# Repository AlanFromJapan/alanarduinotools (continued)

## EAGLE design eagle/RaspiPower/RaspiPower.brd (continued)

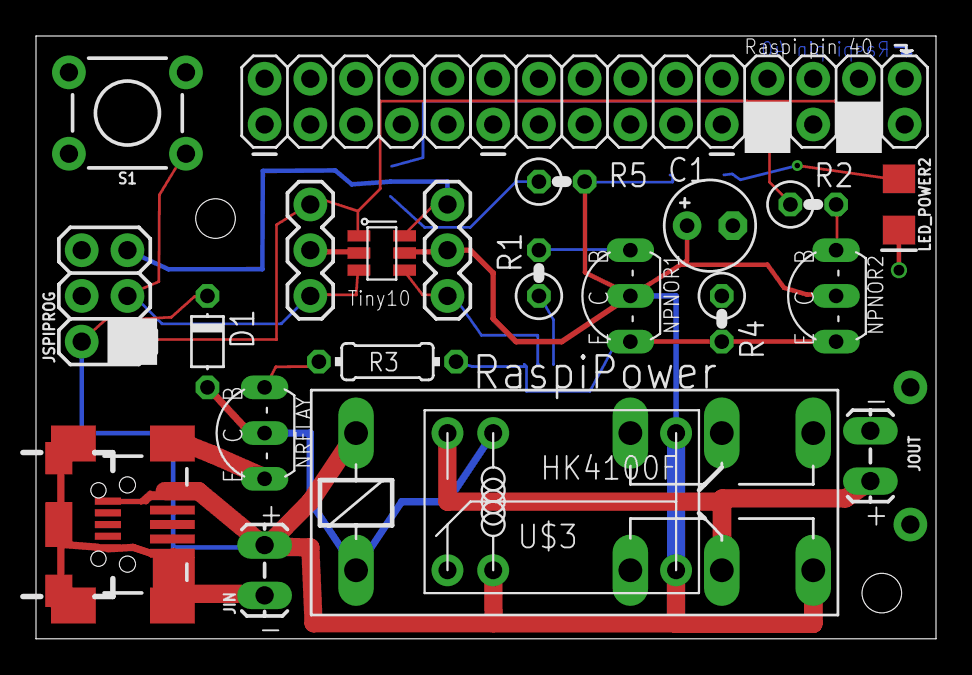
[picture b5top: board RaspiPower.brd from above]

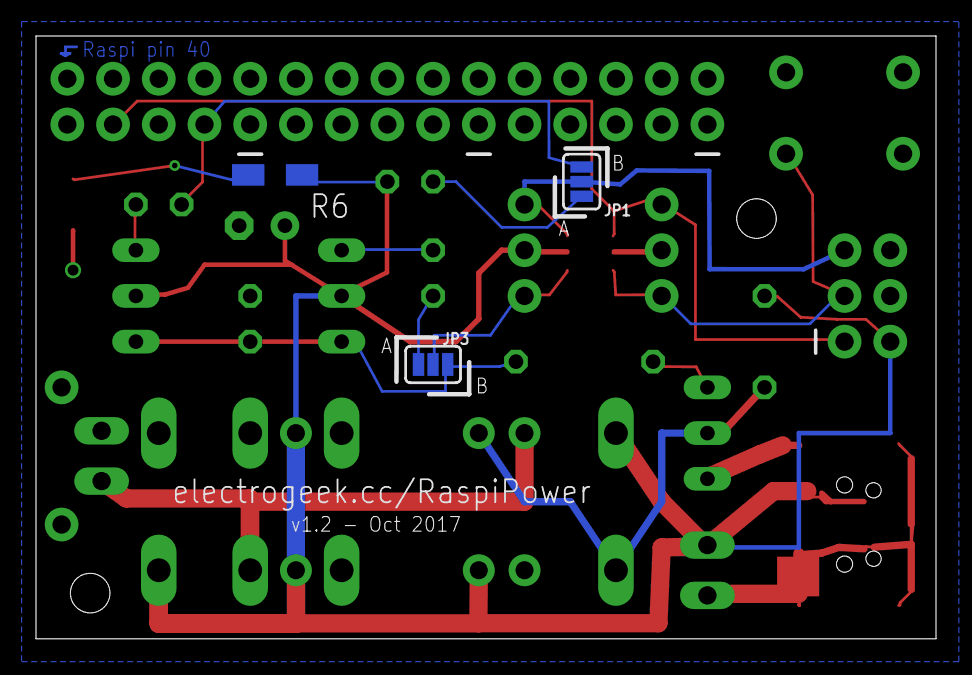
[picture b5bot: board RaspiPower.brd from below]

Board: 2 copper layers, 50.0 x 33.5 mm, 30 parts (3 on the bottom side), 16 nets.

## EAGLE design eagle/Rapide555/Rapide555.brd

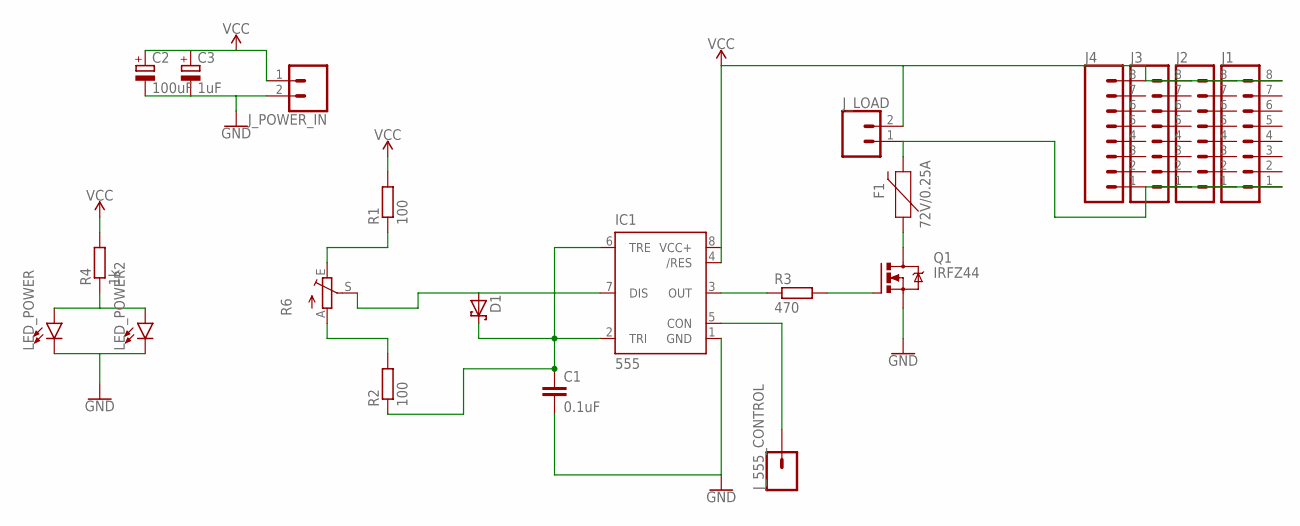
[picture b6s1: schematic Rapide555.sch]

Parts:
C1: 0.1uF; C025-025X050
C2: 100uF; E5-5
C3: 1uF; E2,5-6E
D1: SCHOTTKY-DIODEDO35-7; DO35-7
F1: 72V/0.25A; PTH
IC1: 555; DIP08
J1, J2, J3, J4: CONN_08NO_SILK_FEMALE_PTH; 1X08_NO_SILK
J_555_CONTROL: CONN_01; 1X01
J_LOAD: CONN_023.5MM; SCREWTERMINAL-3.5MM-2
J_POWER_IN: CONN_023.5MM; SCREWTERMINAL-3.5MM-2
LED_POWER: LED3MM; LED_3MM
LED_POWER2: LED-FKIT-1206; FKIT-LED-1206
Q1: IRFZ44; TO-247AD-V
R1: 100; 0204/5
R2: 100; 0204V
R3: 470; 0204/5
R4: 1k; 0204V
R6: TRIM_EU-B25P; B25P

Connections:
GND: C1.2, C2.-, C3.-, IC1.1 (GND), J_POWER_IN.2, LED_POWER.K (C), LED_POWER2.C, Q1.S
unnamed: D1.A, IC1.7 (DIS), R6.S
unnamed: F1.P$2 (2), J1.1, J2.1, J3.1, J4.1, J_LOAD.1
unnamed: F1.P$1 (1), Q1.D
unnamed: IC1.5 (CON), J_555_CONTROL.1
unnamed: IC1.3 (OUT), R3.1
unnamed: Q1.G, R3.2
unnamed: C1.1, D1.C, IC1.2 (TRI), IC1.6 (TRE), R2.1
unnamed: R1.1, R6.E
unnamed: R2.2, R6.A
unnamed: LED_POWER.A, LED_POWER2.A, R4.1
VCC: C2.+, C3.+, IC1.4 (/RES), IC1.8 (VCC+), J1.8, J2.8, J3.8, J4.8, J_LOAD.2, J_POWER_IN.1, R1.2, R4.2

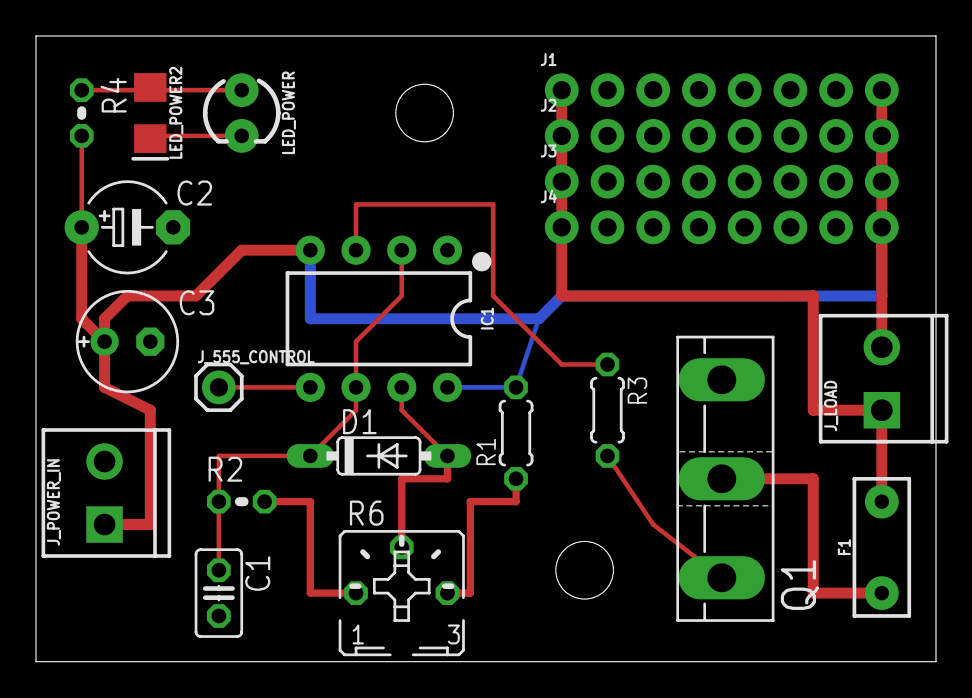
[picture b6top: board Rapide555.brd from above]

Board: 2 copper layers, 50.0 x 34.8 mm, 21 parts (0 on the bottom side), 12 nets.

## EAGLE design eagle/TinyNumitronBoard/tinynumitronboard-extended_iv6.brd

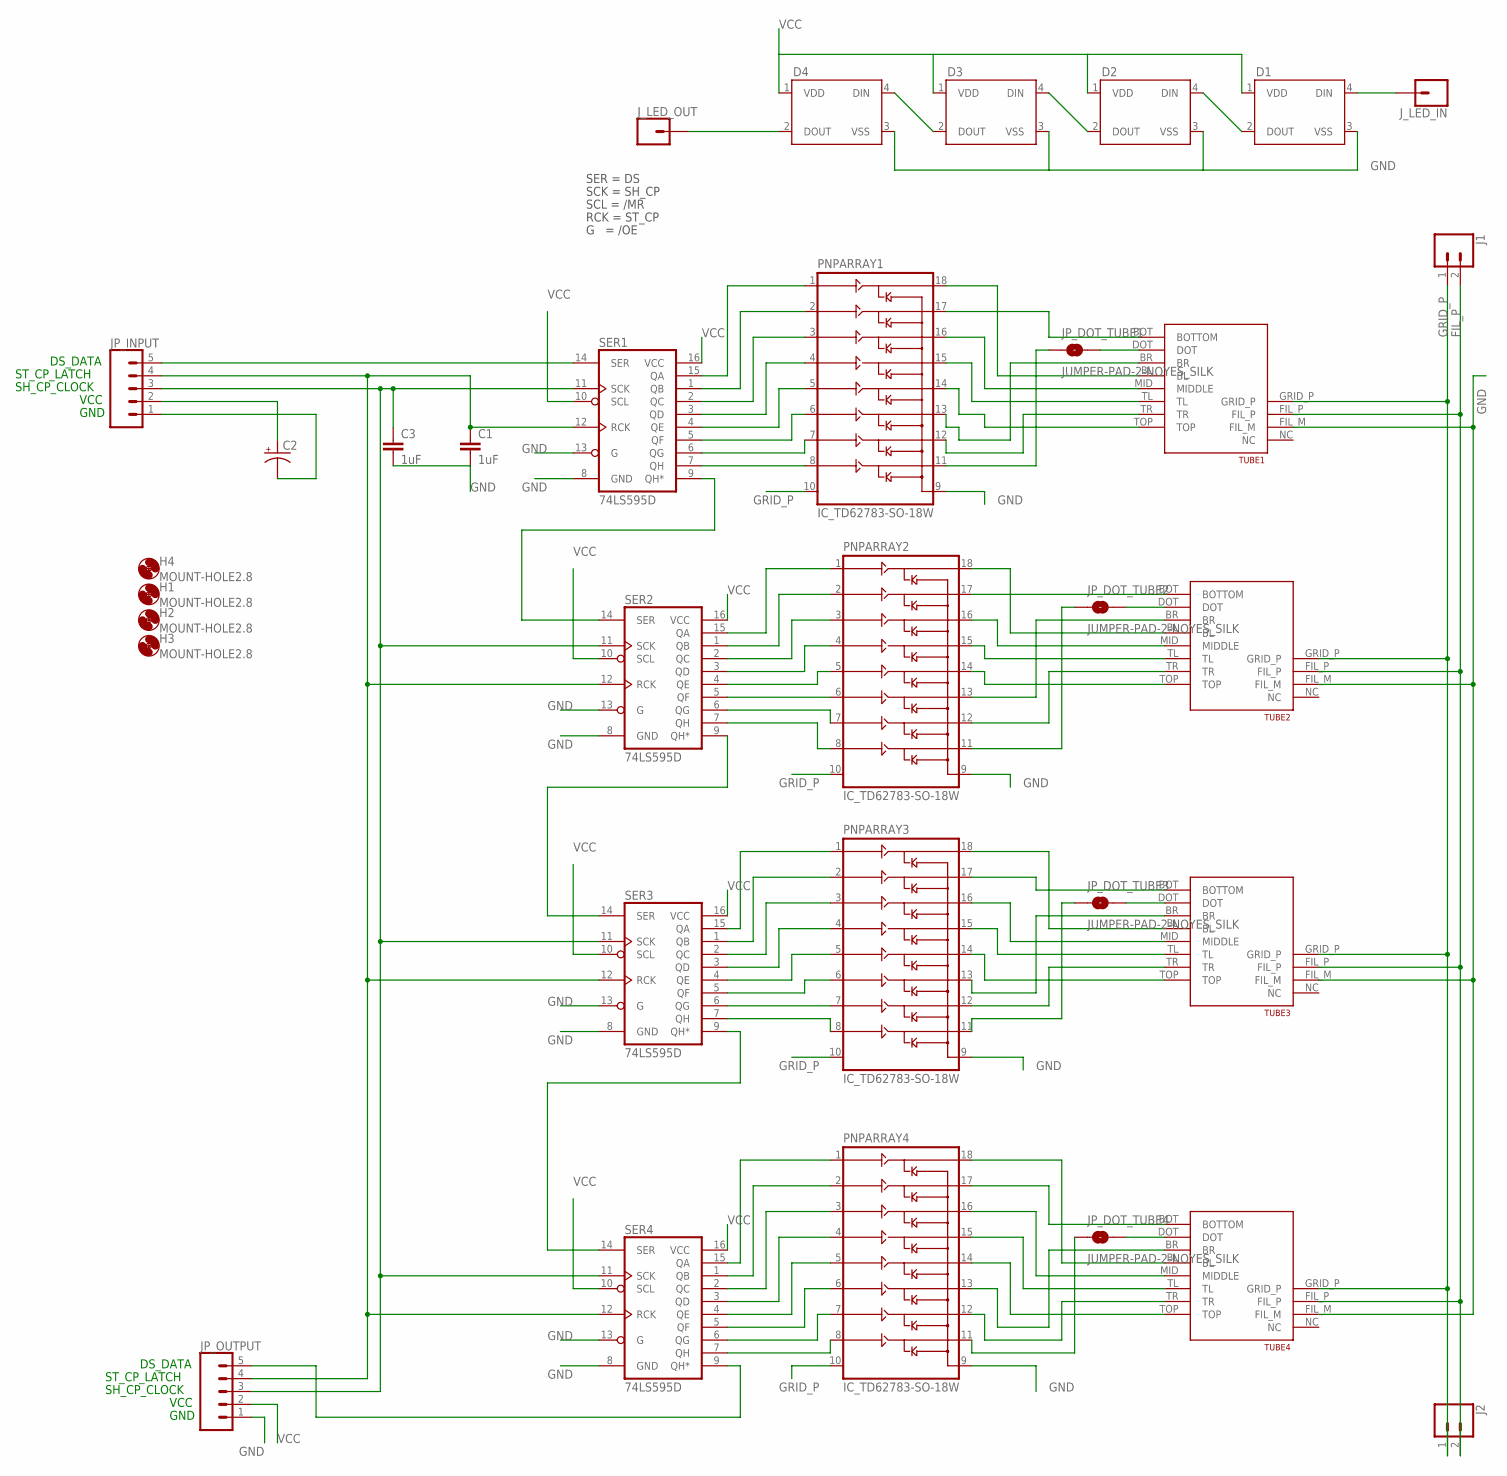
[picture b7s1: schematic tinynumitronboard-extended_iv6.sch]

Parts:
C1, C3: 1uF; C1206
C2: CAP_POLD; PANASONIC_D
D1, D2, D3, D4: WS2812B
H1, H2, H3, H4: MOUNT-HOLE2.8; 2,8
J1, J2: CONN_021X02_NO_SILK; 1X02_NO_SILK
JP_DOT_TUBE1, JP_DOT_TUBE2, JP_DOT_TUBE3, JP_DOT_TUBE4: JUMPER-PAD-2-NOYES_SILK; PAD-JUMPER-2-NO_YES_SILK
JP_INPUT: CONN_05NO_SILK; 1X05_NO_SILK
JP_OUTPUT: CONN_05NO_SILK; 1X05_NO_SILK
J_LED_IN: CONN_01; 1X01
J_LED_OUT: CONN_01; 1X01
PNPARRAY1, PNPARRAY2, PNPARRAY3, PNPARRAY4: IC_TD62783-SO-18W; SO-18L
SER1, SER2, SER3, SER4: 74LS595D; SO16
TUBE1, TUBE2, TUBE3, TUBE4: IV6_NUMITRONLARGE; IV6_NUMITRON_PAC_LARGE

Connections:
FIL_P: J1.2, J2.2, TUBE1.FIL_P, TUBE2.FIL_P, TUBE3.FIL_P, TUBE4.FIL_P
GND: C1.2, C2.-, C3.2, D1.3 (VSS), D2.3 (VSS), D3.3 (VSS), D4.3 (VSS), JP_INPUT.1, JP_OUTPUT.1, PNPARRAY1.9 (GND), PNPARRAY2.9 (GND), PNPARRAY3.9 (GND), PNPARRAY4.9 (GND), SER1.8 (GND), SER1.13 (G), SER2.8 (GND), SER2.13 (G), SER3.8 (GND), SER3.13 (G), SER4.8 (GND), SER4.13 (G), TUBE1.FIL_M, TUBE2.FIL_M, TUBE3.FIL_M, TUBE4.FIL_M
GRID_P: J1.1, J2.1, PNPARRAY1.10 (VS), PNPARRAY2.10 (VS), PNPARRAY3.10 (VS), PNPARRAY4.10 (VS), TUBE1.GRID_P, TUBE2.GRID_P, TUBE3.GRID_P, TUBE4.GRID_P
unnamed: PNPARRAY1.5 (IN5), SER1.4 (QE)
unnamed: PNPARRAY1.4 (IN4), SER1.3 (QD)
unnamed: PNPARRAY1.3 (IN3), SER1.2 (QC)
unnamed: PNPARRAY1.2 (IN2), SER1.1 (QB)
unnamed: PNPARRAY1.1 (IN1), SER1.15 (QA)
unnamed: PNPARRAY1.6 (IN6), SER1.5 (QF)
unnamed: PNPARRAY1.7 (IN7), SER1.6 (QG)
unnamed: PNPARRAY1.8 (IN8), SER1.7 (QH)
unnamed: D1.2 (DOUT), D2.4 (DIN)
unnamed: D2.2 (DOUT), D3.4 (DIN)
unnamed: D3.2 (DOUT), D4.4 (DIN)
unnamed: D1.4 (DIN), J_LED_IN.1
unnamed: SER2.9 (QH*), SER3.14 (SER)
unnamed: PNPARRAY2.18 (OUT1), TUBE2.BL
unnamed: PNPARRAY1.18 (OUT1), TUBE1.BL
unnamed: PNPARRAY2.17 (OUT2), TUBE2.BOT (BOTTOM)
unnamed: PNPARRAY2.16 (OUT3), TUBE2.MID (MIDDLE)
unnamed: PNPARRAY1.17 (OUT2), TUBE1.BOT (BOTTOM)
unnamed: PNPARRAY1.16 (OUT3), TUBE1.MID (MIDDLE)
unnamed: SER1.9 (QH*), SER2.14 (SER)
unnamed: PNPARRAY4.18 (OUT1), TUBE4.BL
unnamed: PNPARRAY4.17 (OUT2), TUBE4.BOT (BOTTOM)
unnamed: PNPARRAY4.16 (OUT3), TUBE4.MID (MIDDLE)
unnamed: PNPARRAY4.15 (OUT4), TUBE4.TL
unnamed: PNPARRAY4.14 (OUT5), TUBE4.TOP
unnamed: PNPARRAY4.13 (OUT6), TUBE4.BR
unnamed: PNPARRAY4.12 (OUT7), TUBE4.TR
unnamed: JP_DOT_TUBE4.1, PNPARRAY4.11 (OUT8)
unnamed: PNPARRAY4.1 (IN1), SER4.15 (QA)
unnamed: PNPARRAY4.2 (IN2), SER4.1 (QB)
unnamed: PNPARRAY4.3 (IN3), SER4.2 (QC)
unnamed: PNPARRAY4.4 (IN4), SER4.3 (QD)
unnamed: PNPARRAY4.5 (IN5), SER4.4 (QE)
unnamed: PNPARRAY4.6 (IN6), SER4.5 (QF)
unnamed: PNPARRAY1.15 (OUT4), TUBE1.TL
unnamed: PNPARRAY2.15 (OUT4), TUBE2.TL
unnamed: PNPARRAY2.14 (OUT5), TUBE2.TOP
unnamed: PNPARRAY2.13 (OUT6), TUBE2.BR
unnamed: PNPARRAY2.12 (OUT7), TUBE2.TR
unnamed: JP_DOT_TUBE2.1, PNPARRAY2.11 (OUT8)
unnamed: PNPARRAY2.1 (IN1), SER2.15 (QA)
unnamed: PNPARRAY2.2 (IN2), SER2.1 (QB)
unnamed: PNPARRAY2.3 (IN3), SER2.2 (QC)
unnamed: PNPARRAY2.4 (IN4), SER2.3 (QD)
unnamed: PNPARRAY2.5 (IN5), SER2.4 (QE)
unnamed: PNPARRAY2.6 (IN6), SER2.5 (QF)
unnamed: PNPARRAY2.7 (IN7), SER2.6 (QG)
unnamed: PNPARRAY2.8 (IN8), SER2.7 (QH)
unnamed: PNPARRAY4.7 (IN7), SER4.6 (QG)
unnamed: SER3.9 (QH*), SER4.14 (SER)
unnamed: PNPARRAY3.18 (OUT1), TUBE3.BL
unnamed: PNPARRAY1.14 (OUT5), TUBE1.TOP
unnamed: PNPARRAY1.13 (OUT6), TUBE1.BR
unnamed: PNPARRAY1.12 (OUT7), TUBE1.TR
unnamed: PNPARRAY3.17 (OUT2), TUBE3.BOT (BOTTOM)
unnamed: JP_DOT_TUBE1.1, PNPARRAY1.11 (OUT8)
unnamed: PNPARRAY3.16 (OUT3), TUBE3.MID (MIDDLE)
unnamed: PNPARRAY3.15 (OUT4), TUBE3.TL
unnamed: PNPARRAY3.14 (OUT5), TUBE3.TOP
unnamed: PNPARRAY3.13 (OUT6), TUBE3.BR
unnamed: PNPARRAY3.12 (OUT7), TUBE3.TR
unnamed: JP_DOT_TUBE3.1, PNPARRAY3.11 (OUT8)
unnamed: PNPARRAY3.1 (IN1), SER3.15 (QA)
unnamed: PNPARRAY3.2 (IN2), SER3.1 (QB)
unnamed: PNPARRAY3.3 (IN3), SER3.2 (QC)
unnamed: PNPARRAY3.4 (IN4), SER3.3 (QD)
unnamed: PNPARRAY3.5 (IN5), SER3.4 (QE)
unnamed: PNPARRAY3.6 (IN6), SER3.5 (QF)
unnamed: PNPARRAY3.7 (IN7), SER3.6 (QG)
unnamed: PNPARRAY3.8 (IN8), SER3.7 (QH)
unnamed: PNPARRAY4.8 (IN8), SER4.7 (QH)
unnamed: JP_DOT_TUBE2.2, TUBE2.DOT
unnamed: JP_DOT_TUBE3.2, TUBE3.DOT
unnamed: JP_DOT_TUBE1.2, TUBE1.DOT
unnamed: JP_DOT_TUBE4.2, TUBE4.DOT
unnamed: JP_OUTPUT.5, SER4.9 (QH*)
unnamed: D4.2 (DOUT), J_LED_OUT.1
RCK: C1.1, JP_INPUT.4, JP_OUTPUT.4, SER1.12 (RCK), SER2.12 (RCK), SER3.12 (RCK), SER4.12 (RCK)
SCK: C3.1, JP_INPUT.3, JP_OUTPUT.3, SER1.11 (SCK), SER2.11 (SCK), SER3.11 (SCK), SER4.11 (SCK)
SER: JP_INPUT.5, SER1.14 (SER)
VCC: C2.+, D1.1 (VDD), D2.1 (VDD), D3.1 (VDD), D4.1 (VDD), JP_INPUT.2, JP_OUTPUT.2, SER1.10 (SCL), SER1.16 (VCC), SER2.10 (SCL), SER2.16 (VCC), SER3.10 (SCL), SER3.16 (VCC), SER4.10 (SCL), SER4.16 (VCC)

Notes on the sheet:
SER = DS
SCK = SH_CP
SCL = /MR
RCK = ST_CP
G = /OE
GND
VCC
SH_CP_CLOCK
ST_CP_LATCH
DS_DATA

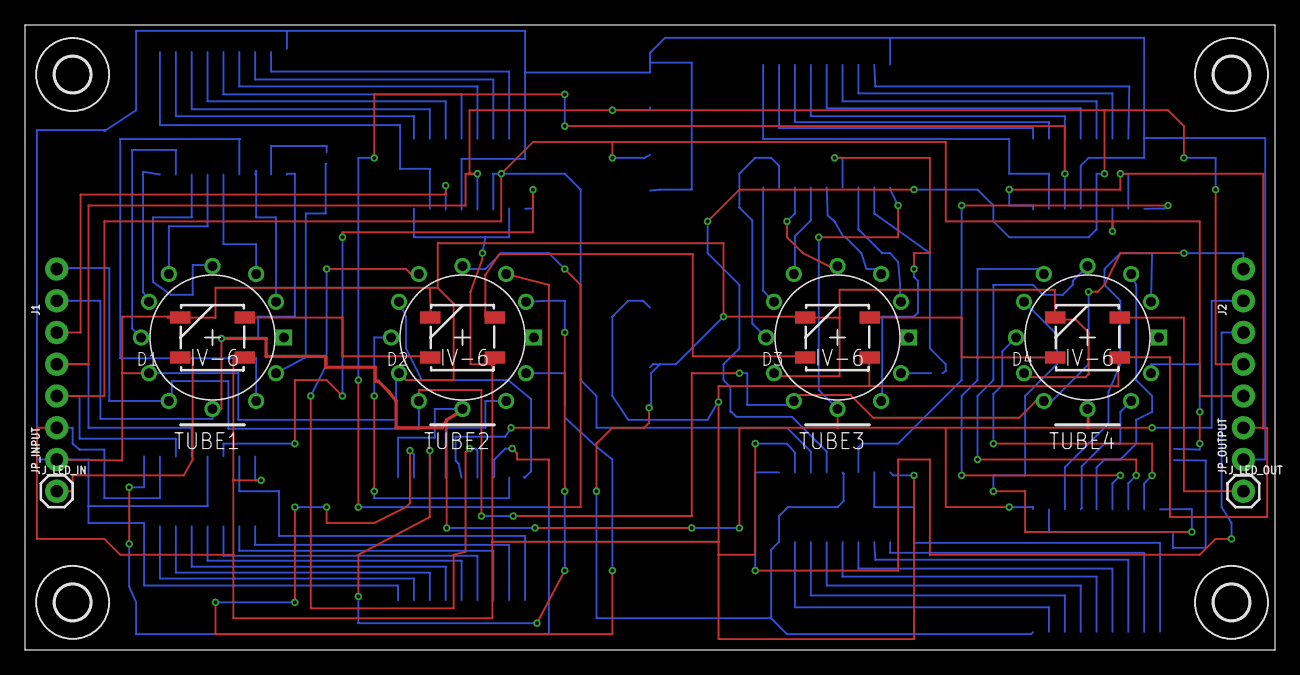
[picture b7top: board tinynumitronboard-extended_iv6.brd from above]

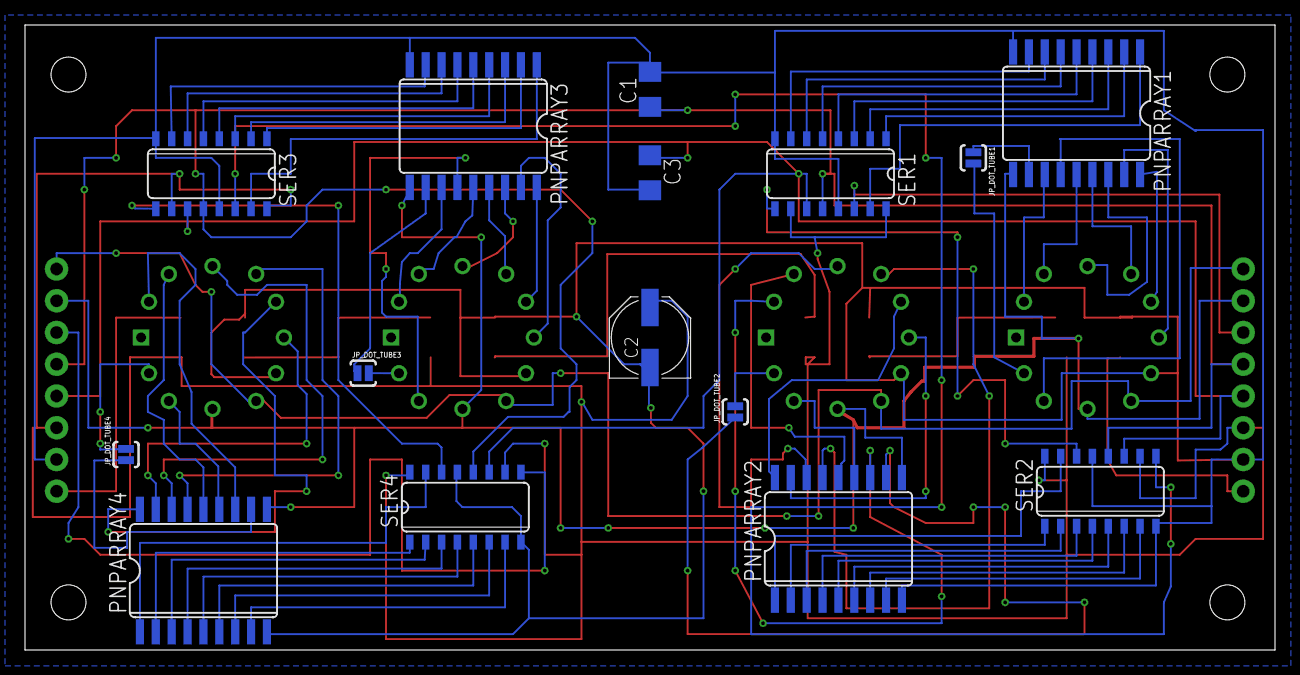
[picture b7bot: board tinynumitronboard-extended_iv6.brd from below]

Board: 2 copper layers, 100.0 x 50.0 mm, 34 parts (15 on the bottom side), 84 nets.

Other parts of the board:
U$1: SNOW1_1000X500

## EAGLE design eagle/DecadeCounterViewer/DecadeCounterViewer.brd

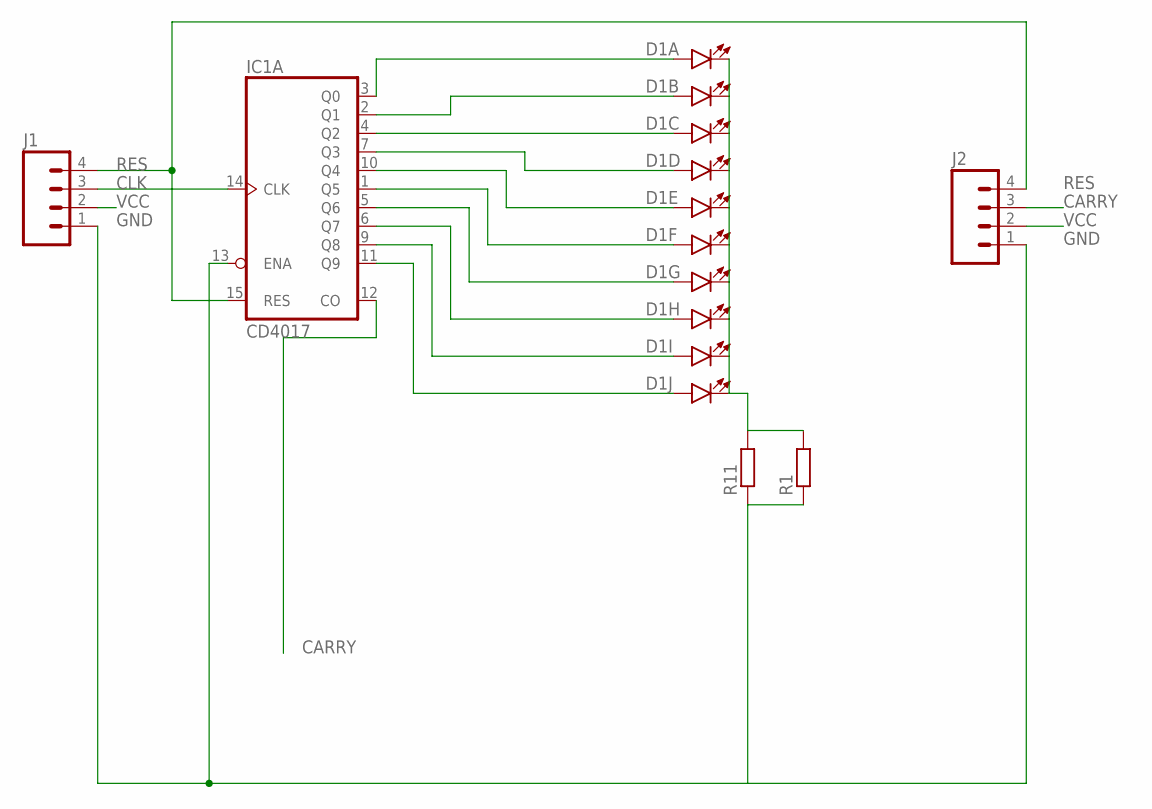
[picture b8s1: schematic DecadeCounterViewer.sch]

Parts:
D1: LED_BARGRAPH_10; LED_BARGAPH_10
IC1: CD4017; DIL16
J1, J2: M04LOCK; 1X04_LOCK
R1: R-EU_0204/7; 0204/7
R11: R-EU_R1206; R1206

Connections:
CARRY: IC1.12 (CO), J2.3
CLK: IC1.14 (CLK), J1.3
GND: IC1.8 (GND), IC1.13 (ENA), J1.1, J2.1, R1.1, R11.1
unnamed: D1.11 (C), D1.12 (C), D1.13 (C), D1.14 (C), D1.15 (C), D1.16 (C), D1.17 (C), D1.18 (C), D1.19 (C), D1.20 (C), R1.2, R11.2
unnamed: D1.1 (A), IC1.3 (Q0)
unnamed: D1.2 (A), IC1.2 (Q1)
unnamed: D1.3 (A), IC1.4 (Q2)
unnamed: D1.4 (A), IC1.7 (Q3)
unnamed: D1.5 (A), IC1.10 (Q4)
unnamed: D1.6 (A), IC1.1 (Q5)
unnamed: D1.7 (A), IC1.5 (Q6)
unnamed: D1.8 (A), IC1.6 (Q7)
unnamed: D1.9 (A), IC1.9 (Q8)
unnamed: D1.10 (A), IC1.11 (Q9)
RES: IC1.15 (RES), J1.4, J2.4
VCC: IC1.16 (VCC), J1.2, J2.2

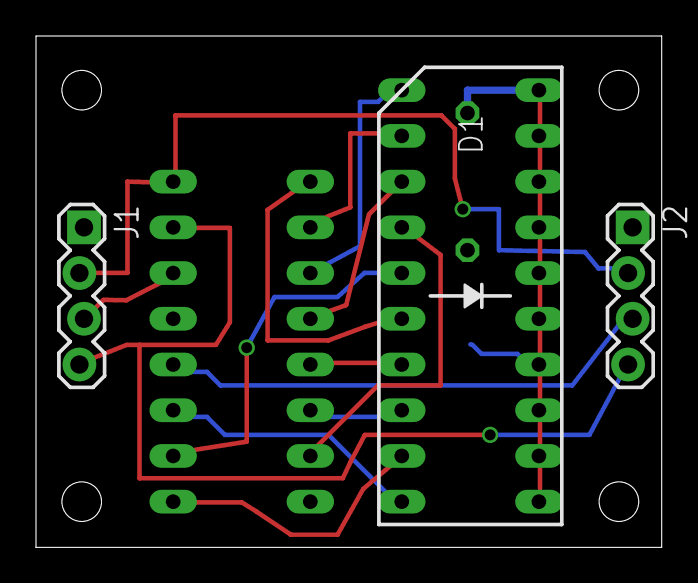
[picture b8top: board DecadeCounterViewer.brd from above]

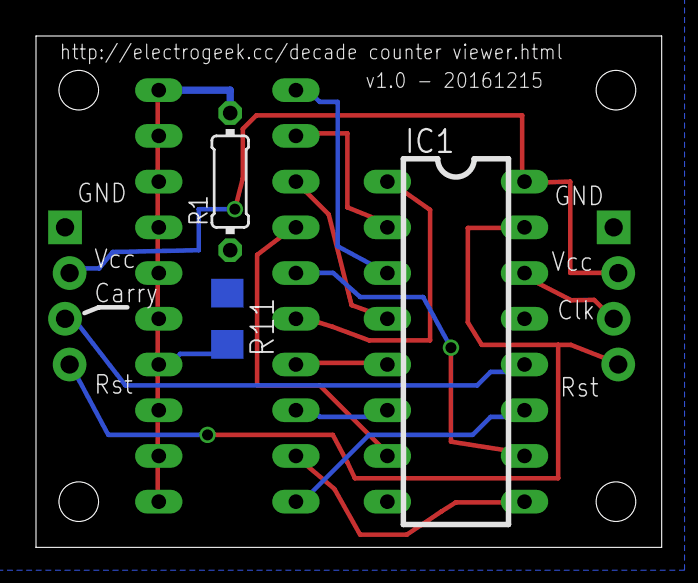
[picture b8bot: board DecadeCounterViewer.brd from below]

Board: 2 copper layers, 34.8 x 28.4 mm, 6 parts (3 on the bottom side), 16 nets.

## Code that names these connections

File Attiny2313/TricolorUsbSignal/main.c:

/* Name: main.c
 * Project: TricolorUsbSignal http://kalshagar.wikispaces.com/Tricolor+USB+alert
 * Author: AlanFromJapan (Dec 2014)
 * Source Project: ThingM.Blink(1)
 *
 * blink(1) - BlinkM-like device with USB interface
 *  2012, Tod E. Kurt, http://thingm.com/ , http://todbot.com/blog/
 *
 * Based on much code from:
 *   Project: hid-custom-rq example by  Christian Starkjohann
 *   LinkM : http://linkm.thingm.com/
 *
 *
 * Note: blink(1) contains no code from BlinkM.  The circuit is different,
 * the PWM is hardware, not software, and the fading and pattern engine work
 * differently.
 */

#define F_CPU 12000000
#include <avr/io.h>
#include <util/delay.h>     // for _delay_ms()
#include <avr/interrupt.h>
#include <avr/pgmspace.h>
#include <avr/wdt.h>

#include "usbdrv.h"
#include "Keyboard.h"
#include "vusb-config.h"

/* ----------------------- hardware I/O abstraction ------------------------ */

/* pin assignments:
PB0	Key 1
PB1	N/A
PB2	N/A
PB3 N/A
PB4	N/A
PB5 red LED
PB6 yellow LED
PB7	green LED

PA0 N/A
PA1 N/A

PD0	N/A
PD1	debug tx ?
PD2	USB+ (int0)
PD3	N/A
PD4	USB-
PD5	N/A
PD6	N/A
*/

static void hardwareInit(void)
{
	uint8_t	i, j;

	PORTB = 0x00;   //no pullups
	DDRB = 0xff;    //all outputs

	PORTD = 0xfa;   /* 1111 1010 bin: activate pull-ups except on USB lines */
	DDRD = 0x07;    /* 0000 0111 bin: all pins input except USB (-> USB reset) */
	j = 0;
	while(--j){     /* USB Reset by device only required on Watchdog Reset */
		i = 0;
		while(--i); /* delay >10ms for USB reset */
	}
	DDRD = 0x02;    /* 0000 0010 bin: remove USB reset condition */
	/* configure timer 0 for a rate of 12M/(1024 * 256) = 45.78 Hz (~22ms) */
	TCCR0A = 5;      /* timer 0 prescaler: 1024 */
}


/* ------------------------------------------------------------------------- */

int main(void) {
    wdt_enable(WDTO_1S);  // watchdog status is preserved on reset


    hardwareInit();
    
    usbInit();
    usbDeviceDisconnect();

    // fake USB disconnect for > 250 ms
    for( uint8_t i=255; i>0; i-- ) {
	    wdt_reset();
	    _delay_ms(1);
    }
    usbDeviceConnect();

    sei();

    for(;;){                // main event loop
		wdt_reset();
		usbPoll();
    }	
	
	return 0;
}

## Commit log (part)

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2015-01-25 POV duration can be overridden at include time
2015-01-25 Bugfix, one method was declared after its caller, which panicked C compiler.
2015-01-27 Added lots of classes (data model) and viewing. Now can view, extract to list, and show under different modes (zoom or tiled)
2015-01-31 Can read and save to xml the library and its sprites.
2015-02-01 Added new class for double buffered panel. Tile edition (basic version) working ok now.
2015-02-01 Tilizator function beta ok
2015-02-01 Fixed palette matching issue, added tilization reuse function (avoid creating too much tiles).
2015-02-01 Fixed the Fill function. Fixed the ROM viewer selector.
2015-02-05 New project for GB cartridge controller
2015-02-11 Still not writing, before trying the internet guy suggestion
2015-02-19 Fix: paint when click on pixel in tile editor, not on move only
2015-05-17 Migrating wiki contents from Google Code
2015-07-08 Test serial communication (echo sample with interrupt) working fine :)
2015-07-13 Test with button on C1 ok even on USB
2015-07-19 Added a sample VUSBKeyboard project and a python script for making easily names of products as a char array.
2015-07-20 much more keycodes and a working way to send strings char by char to PC! Problem: key mapping. My Japanese keyboard is not mapped as per the definition and some characters like ampersand or parenthes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
2015-07-20 Minor edit (cosmetic)
2015-08-13 Added multiple functions for Finger print scanner in FPS.c. Now can send commands to FPS and type result as a keyboard for debug. Next step is a full enrollment and then check.
2015-08-15 Added ignore host pattern in the config file
2015-08-16 Moving constants around, minor changes. Attempt to have C5 drive a high side PNP to turn off the FPS: control is working ok but the FPS doesn't turn off... mystery.
2015-08-17 Forgot to embed the icon
2015-08-25 4 buttons and sample passwords (added gitignore to ignore the file that holds the passwords). Need a small negative feedback on error (vibrator or led?) and a small code cleanup and it will be finish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
2015-08-29 Added usbDelayMs() to delay and keep USB alive
2015-09-03 Added python flask engine for website (WIP)
2015-09-03 Added a in-memory caching, but couldn't find significant improvement in speed. Need to add timeout function.
2015-09-16 Routed ok, need labelling
2015-11-01 Seaphone rotary reading (basic), prog core (not working yet)
2015-11-05 Code complete but not working ... start debuging
2015-11-07 Debuging: one step further, now impulse properly registered: my maths for the delay were way off! divided by a factor 10, we got good measurement now. Next, digit separation must be off (depended on 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
2015-11-09 Seaphone diagrams
2015-11-09 Ignore some other files of Eagle and .atsuo files
2015-11-10 Added special case of 0 input
2016-01-24 Added SmokeyAmp plans
2016-04-29 Added sample http server, and now communication is ok
2016-04-30 added better helper function for the LUA script (arduino will jsut have to send the json object). Added a sample python program to emulate request, works fine.
2016-04-30 Cleaned up version, remains to plug on arduino or something alike now.
2016-05-06 Tested (but failed) project for the Kodi-remote. Store in case there's some ideas for future.
2016-05-07 Added project for Kodi_remote (this time it's the good one I hope!)
2016-05-10 Fixed problem with timing: oscillator speed depends on voltage
2016-06-25 v1.0 of dessinaka bin because gmail forbids me to send it
2016-10-30 Started the LiionDrillCharger code witn an Attiny26
    Just a blink program for now but it works on the uc
2016-11-03 Sample program that circles through leds and relays
2016-11-19 All code is nearly here, still some problem.
2016-11-19 Added drill lion-charger schematics
2016-12-03 New library for driver ULN2803
    Found on the net, not from me. Thanks for sharing.
2016-12-03 I made a mistake and PC2 is in fact not connected
    Since I won't make another batch and that routing that one wire looks
    like a nightmare, I just remove it from schematics to avoid confusion
    later. A good lesson learnt.
2016-12-03 Layout first draft finished.
    Todo review.
2016-12-03 added pad for UL2803 diode/common
2016-12-03 Still optimizing/reviewing
2016-12-03 Still still continued ...
    Need top and bottom text layer + image
2016-12-04 Final save before top layer art
2016-12-04 Last changes but problem with drill holes
2016-12-04 Added the zip sent to prod to Seeedstudio
2016-12-04 Quick and dirty PoC but working
    Scavenged sample code of V-USB for volume control. it works with only
    minor tweaks. Need to read the encoder now.
2016-12-06 Rotary encoder working as beta for volume control!
    Code is UGLY but it's just a beta now. Need to do a cleanup, and then
    start preparing the physical device.
2016-12-09 Added 2 alternate SMD 22pF caps
    That makes 2 airwire because I can't attach to the pad center, but once
    made the connection should be all ok.
2016-12-10 Minor changes and comments
2016-12-11 Decade counter continued
2016-12-15 Added cam job and some slight changes
2016-12-15 Sent to production to seeedstudio
2017-01-07 Crapped up, now fixing
    Started version 2, ripped up everything
2017-01-07 Manual wiring WiP (30%)
2017-01-08 Got a better hold on the logic
    Implementation in progress
2017-01-08 Now working ok, but need some improvements.
2017-01-08 added bach file to run test on linux.
2017-01-08 After first pass of EagleGridFixer
    Result look ok but in case
2017-01-09 Before running script for 2nd time
2017-01-09 Wiring continued (95%)
2017-01-09 Removed LEDs for colon
2017-01-09 Wiring finished, DRC ok
    Before last run of script
2017-01-14 Added ESP8266 SonOff script
2017-01-15 Added SonOff basic script
2017-09-01 Added brd for Rapide555 (still WIP)
2017-09-01 Rapide555 minor changes.
2017-09-03 Rapide555 v1.0 as sent to production
2017-09-06 Dust counter v1.0 and .hex file
2017-09-16 edited the Raspipower schematics, some review of components to do before moving to the board design.
2017-09-18 Draft placement, now on to the routing
2017-09-18 Routing looks ok, now todo final review and board silk
2017-09-18 RaspiPower v1.0 ready for production
2017-10-03 fixed the bit operations funcs
2017-10-08 Still fixing the board, not finished
2017-10-12 RaspiPower code working
    Simple version, just timeout for shutdown
2017-10-14 Some sample of sliding text, working
2017-10-25 Changed things that should not be important, rollback some in case...
2017-10-31 Typo fix
2018-05-08 Changed the DNS accueil script, working fine now, just a final cosmetic before deployment.
2018-11-20 added first files for the EInk Weather station
2018-11-23 Layout making good progress
2018-12-24 Added possible moon phase calculation and 2 images
2019-02-09 test folder and files for weatherbit.io service
2019-02-11 Added 2 more logo for weather
2019-02-14 Night time will show different icons.
2019-02-20 Mostly rewrite and added code for 2 buttons (skeletton). Now will implement panels.
2019-02-20 Added autorefresh and shutdow enabled
2019-02-21 Fixed the "end" image, background must be TRANSPARENT not white (otherwise all becomes black on the screen)
2019-03-16 make sure that LED is OFF after it turns on thursdays
2019-04-04 started to break down the app in different module, separate interface and more basic drwaing etc... well, just rewrtiting it the right way. THEN I will be able to do that interface change I want.
2019-05-08 square designer mostly done, to be finalized.
2019-05-30 Fixed the code to run with the eInk: added the missing rotate parameter to expand, needed to remove PIL and upgrade pillow, and other minor things. It's working now.
2019-05-30 Removed a warning by removing useless global
2019-12-14 Added the project for USB mini keyboard, to be tested. (ECLIPSE project)
2019-12-16 Finally code works, some inequalities in the wrong sense and little refactoring.
2019-12-16 Improved script.
2019-12-18 basic stub of the Attin13 project on Eclipse.
2019-12-19 Added relay toggle: works, but needs to be implemented as a safer version.
2020-01-03 Longpress to turn on with automaton status.
2020-01-18 Errors on getting weather are now displayed on the screen too.
2020-01-18 Implemented "later" weather from OpenWeatherMap. Added logo on boot. Fixed bug on night/day image selection.
2020-01-21 WIP on interface, time to sleep.
2020-01-23 Screen class, radio enumeration and "fake" play pause working
2020-01-25 shudown ok
2020-02-01 Finally autostart with pulseaudio as system wide service WORKS.
2020-02-02 Now playing the startup sound is asynchronous (way better)
2020-02-03 Files for Vision API test
2020-02-18 beta of the SNES2USB PCB
2020-02-23 Before resuming working on RapiedUSBII, a quick commit of whatever I did.
2020-03-01 Rewrote the YMZ294 test as .ino
2020-03-08 USB D- is D4, like default of the PCB (solder bridge)
2020-03-10 Added test code
2020-03-15 Save if no project becomes Save as.
2020-03-15 Now export has index and defines set if there was a name for the tile.
2020-03-16 Default palette is now a greenish one
2020-03-19 RapideUSB II sample code checked in.
2020-03-19 minor fix
2020-03-21 Change tile order on import for easier usage in C later
2020-03-21 Now can paint 4 tiles at a time in a convenient pattern.
2020-03-26 Added option to allow import of duplicated tile
2020-03-26 Latest version of the exe
2020-03-31 Now load properly clears old maps
2020-03-31 Saved bin for later use
2020-03-31 Saved bin
2020-04-03 More stuffs, started implemetation of ROM download
2020-04-05 ignore .vs/ folder, some misc eagle board changes
2020-04-05 ROM Upload, then download works and gives identical files! Success!!
2020-04-07 Raised the speed to 56k, writing 32k in 5 minutes now, tested ok.
2020-04-21 Added latest GbReaper.exe
2020-04-22 Fixed a f***ing mistake that the generated template imported the library .c instead of the .h
2020-04-22 Latest version of the binary with PNG export
2020-04-26 Bugfix in case user cancels map duplication
2020-05-02 New Pigman logo, Victory GB cartridge in last round of review
2020-05-04 Now maps exports to PNG too
2020-05-06 Added Floyd Steinberg dither for tilizator
2020-05-16 Removed warning. Reenable reorder on tile library component.
2020-05-28 Ultima GB cart looks fine and ready to prod. Will avoid to rush and post to the GB forum for feedback.
2020-05-28 Moved the EAGLE projects to a dedicated repo, keep history though (in case).
2021-07-03 Added the MUTE speaker code.
2022-10-19 Added script to generate image to print sequential cards. Works for int now.
2023-09-15 Added support for ATmega8 micro-controller. Detection is not automated yet (must set the #define). Added Eclipse C + Avr config files.
2023-09-15 Missed to remove the unused preprocessor define.
2023-09-22 Cleaned the pullups on C port, added blink when read controller
2024-03-21 Blink for Attiny85
2024-04-22 Color changer I made last year ... no memories of it.
2024-04-22 Fixed interrupt ovf usage, now called 10-20 times a sec.
    (too lazy to calculate).
2024-04-23 Getting closer, still not reading right but close.
2024-04-23 Cosmetic: fixed comment error
2024-04-24 Bugfix the base is not always 10
2024-04-25 Calculation *seems to* work, now todo add k/m indicators
2024-04-30 Working! Calculations ok in base 10.
2024-04-30 No need to press C to enter next resistor values
2024-06-07 Fixed animation, mixed code cleanup
2024-06-07 Updated the bin
2024-06-07 Added updated bin
2026-02-15 Working version (at last!). Works fine on Samsung smartphone, play/pause and Next
2026-04-17 Added feature to set a label for the sonoff and store in EEPROM. as it is coded it is a mjor security leak (buffer overflow) so don't let that be accessible on the internet anywhere. But it works.
2026-05-17 Added the Hatteker battery fakery thing. Initial commit, it builds but not even tested in bench yet.
